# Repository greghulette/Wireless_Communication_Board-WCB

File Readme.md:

<h1 style="display:inline; height: 75px; font-size:51px;">Wireless Communication Board (WCB)</h1>

<br>

# Software 3.0 and newer release changes the command structure.  Please read below to ensure proper operations.  

**NEW WIKI created to help better orgainize the documenation.  It can be found at the top the page or by clicking this link: [WCB Wiki](https://github.com/greghulette/Wireless_Communication_Board-WCB/wiki/)**

<br>
<br>
<br>
<br>
<br>

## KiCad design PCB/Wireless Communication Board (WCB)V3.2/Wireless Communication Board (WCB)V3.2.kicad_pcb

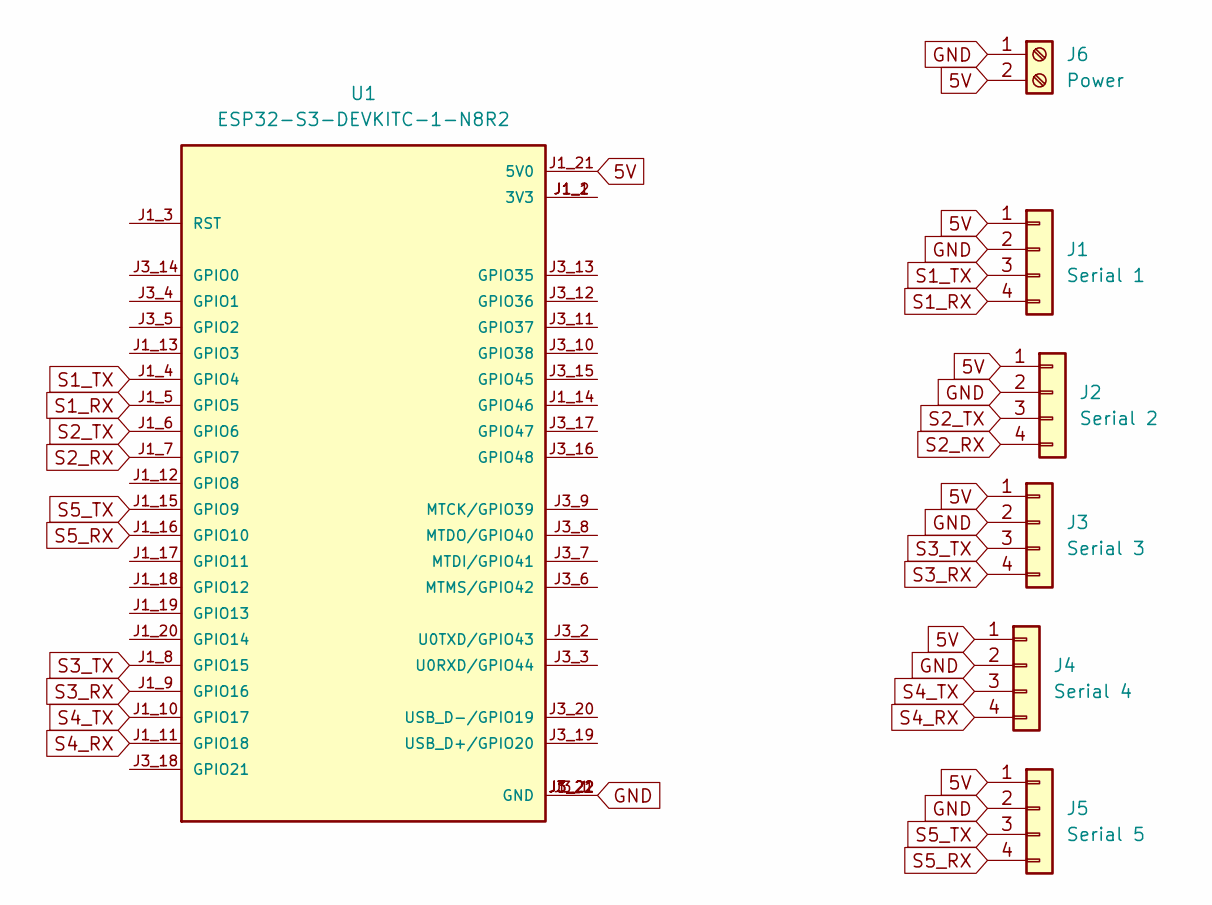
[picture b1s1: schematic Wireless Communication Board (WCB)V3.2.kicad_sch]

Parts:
J1: Serial 1; PinHeader_1x04_P2.54mm_Vertical
J2: Serial 2; PinHeader_1x04_P2.54mm_Vertical
J3: Serial 3; PinHeader_1x04_P2.54mm_Vertical
J4: Serial 4; PinHeader_1x04_P2.54mm_Vertical
J5: Serial 5; PinHeader_1x04_P2.54mm_Vertical
J6: Power; TerminalBlock_Phoenix_MKDS-1,5-2-5.08_1x02_P5.08mm_Horizont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
U1: ESP32-S3-DEVKITC-1-N8R2; XCVR_ESP32-S3-DEVKITC-1-N8R2; PARTREV V1

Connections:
5V: J1.1, J2.1, J3.1, J4.1, J5.1, J6.2, U1.J1_21 (5V0)
GND: J1.2, J2.2, J3.2, J4.2, J5.2, J6.1, U1.J1_22 (GND), U1.J3_1 (GND), U1.J3_21 (GND), U1.J3_22 (GND)
unnamed: U1.J1_1 (3V3), U1.J1_2 (3V3)
S1_RX: J1.4, U1.J1_5 (GPIO5)
S1_TX: J1.3, U1.J1_4 (GPIO4)
S2_RX: J2.4, U1.J1_7 (GPIO7)
S2_TX: J2.3, U1.J1_6 (GPIO6)
S3_RX: J3.4, U1.J1_9 (GPIO16)
S3_TX: J3.3, U1.J1_8 (GPIO15)
S4_RX: J4.4, U1.J1_11 (GPIO18)
S4_TX: J4.3, U1.J1_10 (GPIO17)
S5_RX: J5.4, U1.J1_16 (GPIO10)
S5_TX: J5.3, U1.J1_15 (GPIO9)

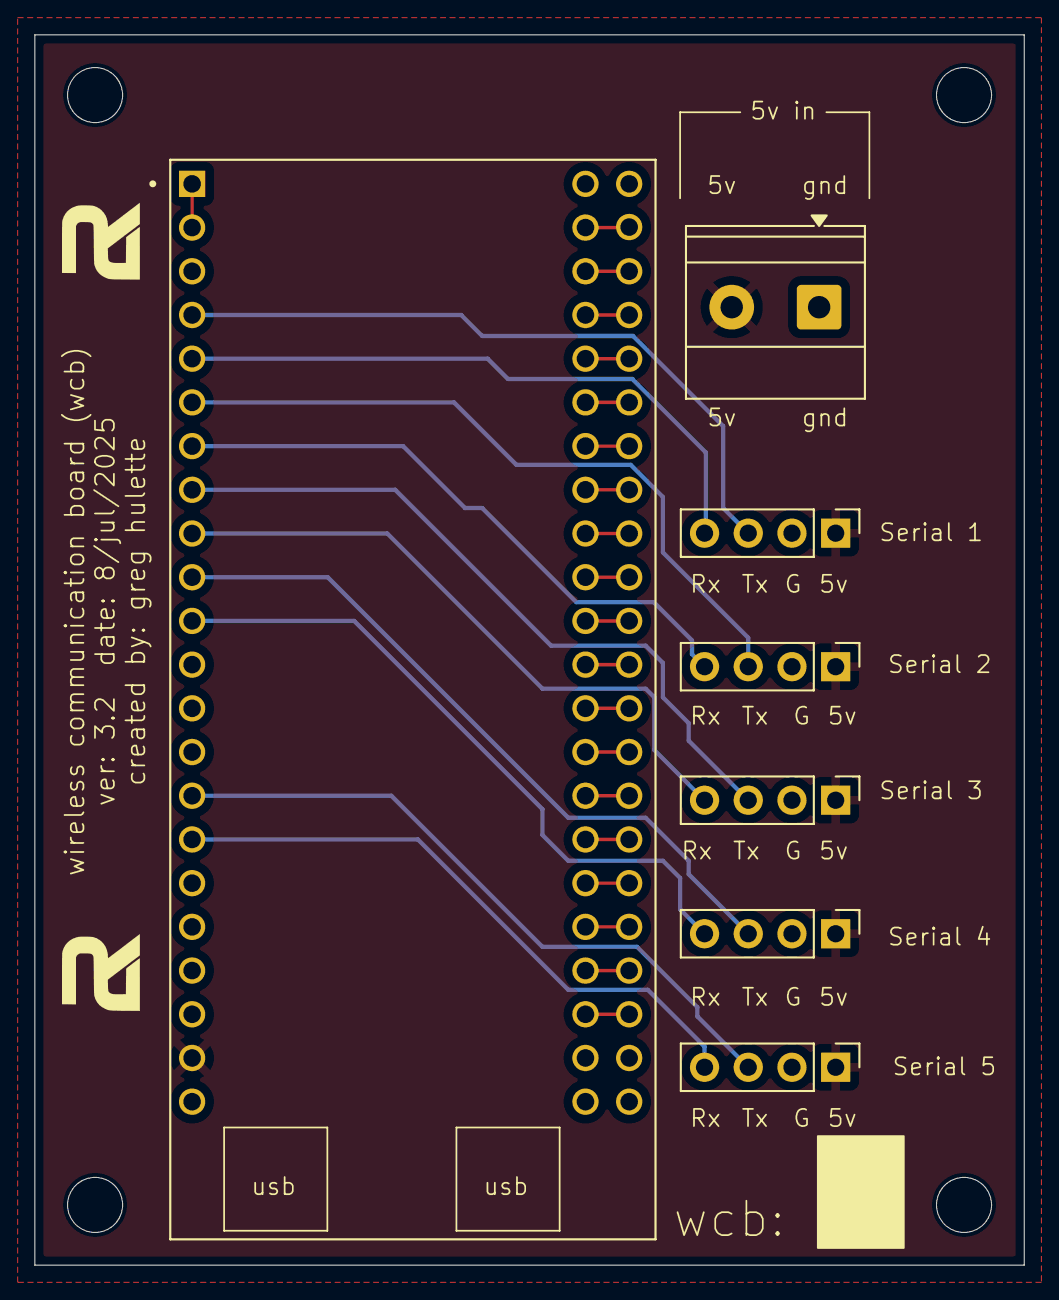
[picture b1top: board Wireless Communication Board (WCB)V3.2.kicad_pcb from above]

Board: 2 copper layers, 57.5 x 71.5 mm, 7 parts (0 on the bottom side), 13 nets.

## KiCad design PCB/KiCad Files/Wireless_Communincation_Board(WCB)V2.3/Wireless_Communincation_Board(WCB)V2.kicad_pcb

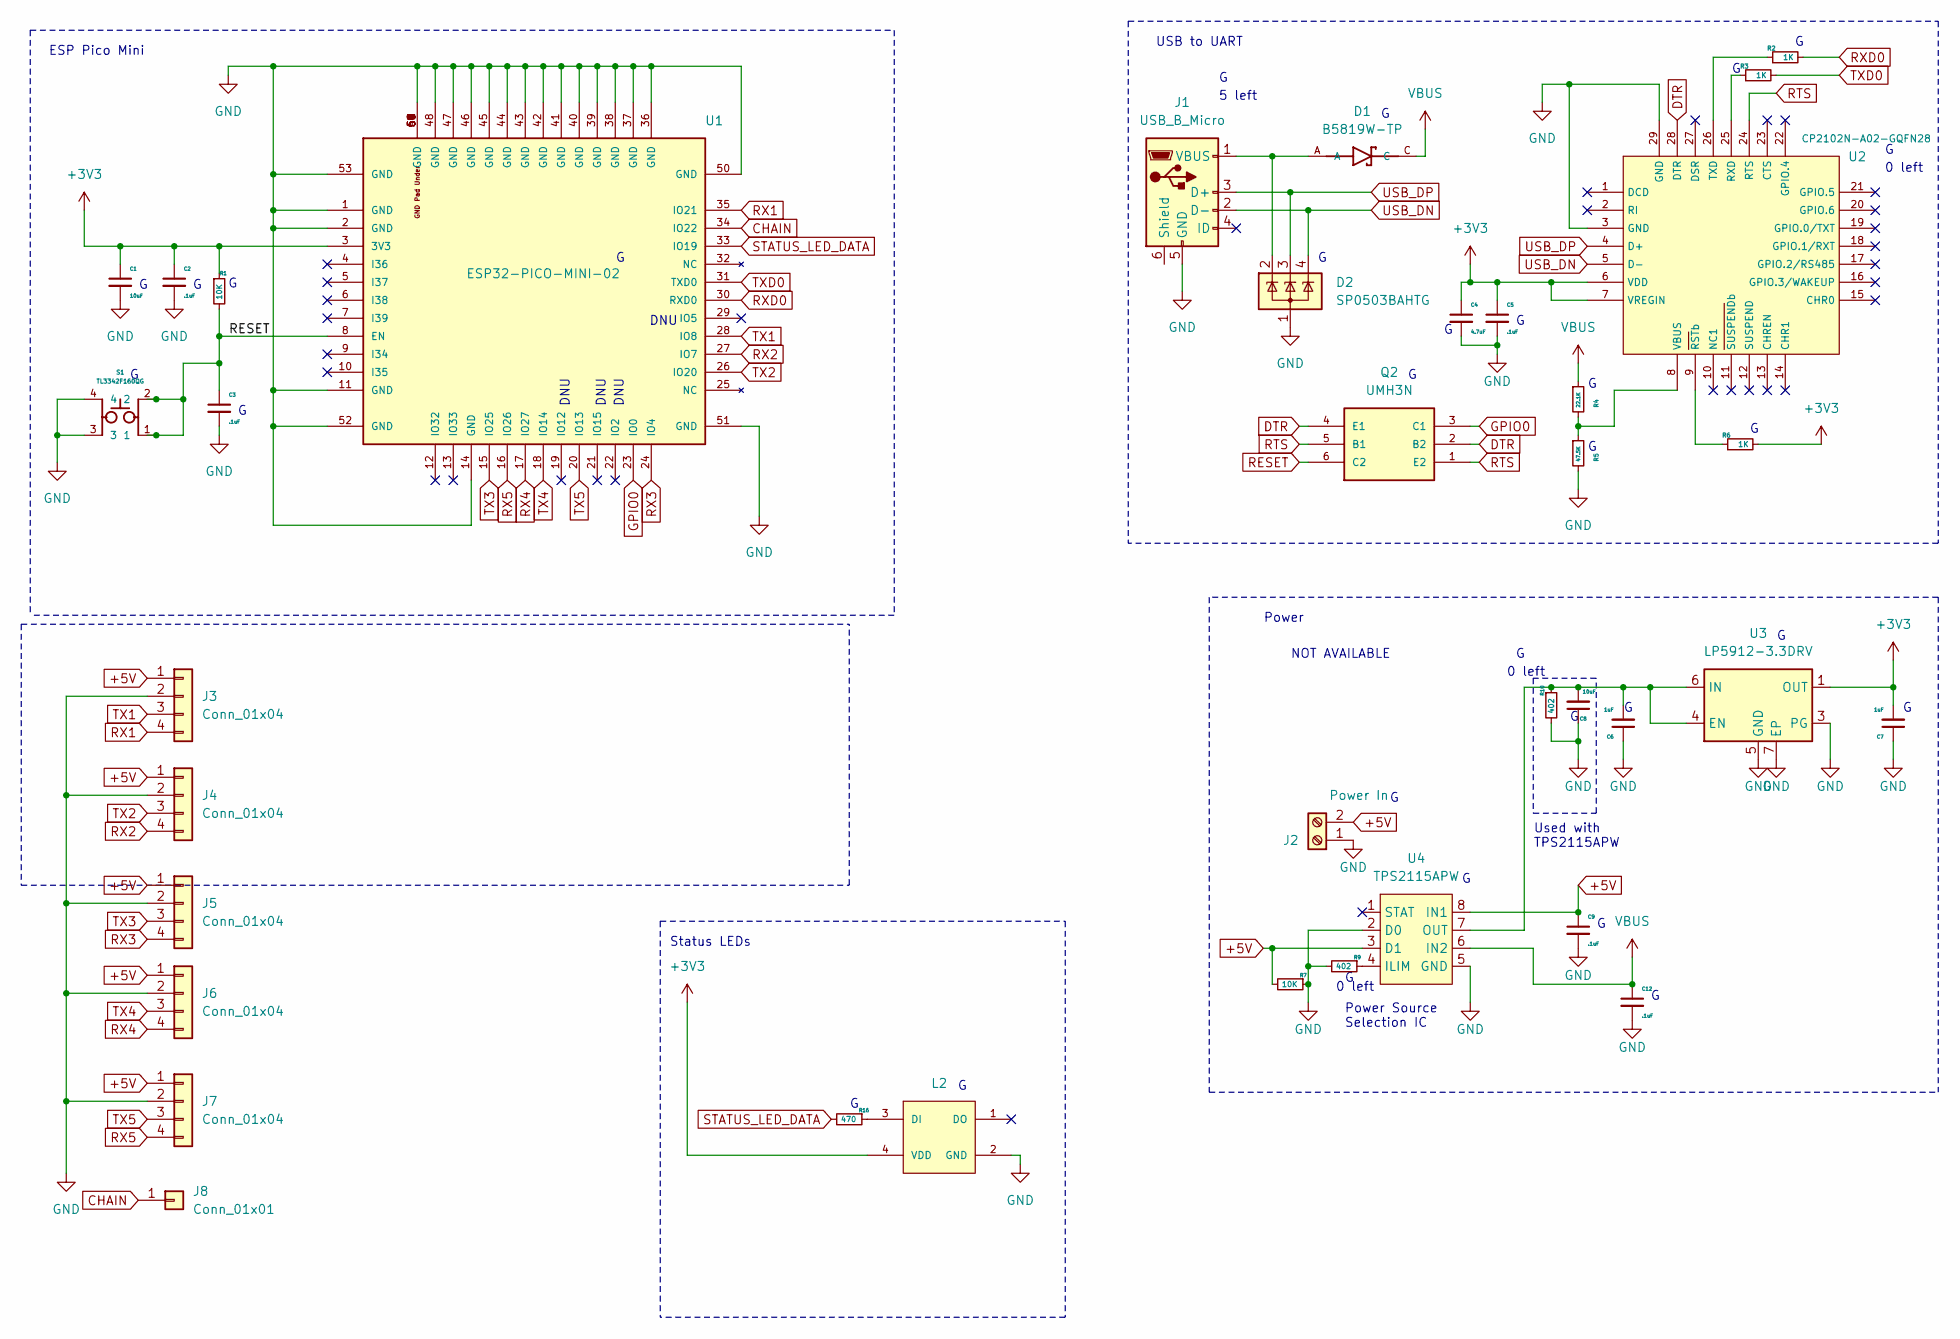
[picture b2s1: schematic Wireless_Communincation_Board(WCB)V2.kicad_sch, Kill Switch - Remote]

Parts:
C1, C8: 10uF; C_0805_2012Metric; Manufacturers Part Numb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 CS2012X7R106K100NRE; LCSC C1222438
C2, C3, C5, C9, C12: .1uF; C_0402_1005Metric; Manufacturers Part Numb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 CL05B104KB54PNC; LCSC C307331
C4: 4.7uF; C_0805_2012Metric; Manufacturers Part Numb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 GCM21BR71C475KA67L; LCSC C126590
C6, C7: 1uF; C_0603_1608Metric; Manufacturers Part Numb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 GRM188B31H105KAALD; LCSC C913562
D1: B5819W-TP; SOD3716X135N; Manufacturers Part Numb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 B5819W-TP; Digikey Part Number B5819W-TPMSCT-ND
D2: SP0503BAHTG; SOT-143; Manufacturers Part Numb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 SP0503BAHTG; Digikey Part Number F2715CT-ND
J1: USB_B_Micro; USB_Micro-B_Amphenol_10118194_Horizontal; Manufacturers Part Numb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 10118194-0001LF; Digikey Part Number 609-4618-1-ND
J2: Power In; TerminalBlock_bornier-2_P5.08mm; Manufacturers Part Numb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 141-A-111/02; LCSC C3011914
J3, J4, J5, J6, J7: Conn_01x04; PinHeader_1x04_P2.54mm_Vertical; LCSC C2691448
J8: Conn_01x01; PinHeader_1x01_P2.54mm_Vertical; LCSC C81276
L2: WS2812B-2020; Manufacturers Part Numb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 WS2812B-2020; LCSC C965555
Q2: UMH3N; SOT65P230X110-6N; MANUFACTURER_PART_NUMBER UMH3N; Digikey Part Number UMH3NTNCT-ND
R1: 10K; R_0402_1005Metric; Manufacturers Part Numb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 RC0402JR-0710KL; Digikey Part Number 311-10KJRCT-ND
R2, R3, R6: 1K; R_0402_1005Metric; Manufacturers Part Numb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 RC0402JR-071KL; Digikey Part Number 311-1.0KJRCT-ND
R4: 22.1K; R_0402_1005Metric; Manufacturers Part Numb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 RC0402JR-0722KL; Digikey Part Number 311-22KJRCT-ND
R5: 47.5K; R_0402_1005Metric; Manufacturers Part Numb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 RC0402FR-0747K5L; Digikey Part Number 311-47.5KLRCT-ND
R7: 10K; R_0402_1005Metric; Manufacturers Part Numb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 AR02DTC1002; LCSC C414854
R9, R10: 402; R_0402_1005Metric; Manufacturers Part Numb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 CR204000F; LCSC C41042
R16: 470; R_0402_1005Metric; Manufacturers Part Numb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 RT0402BRD07470RL; LCSC C114949
S1: TL3342F160QG; SW_TL3342F160QG; Manufacturers Part Numb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 TS-1076S-A6B3; LCSC C492949
U1: ESP32-PICO-MINI-02; MODULE_ESP32-PICO-MINI-02; PARTREV v1.0; Digikey Part Number 1965-ESP32-PICO-MINI-02-N8R2CT-ND
U2: CP2102N-A02-GQFN28; QFN-28-1EP_5x5mm_P0.5mm_EP3.35x3.35mm; Manufacturers Part Numb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 CP2102N-A02-GQFN28; Digikey Part Number 336-5889-ND
U3: LP5912-3.3DRV; WSON-6-1EP_2x2mm_P0.65mm_EP1x1.6mm_ThermalVias; Manufacturers Part Numb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 LP5912Q3.3DRVTQ1; LCSC C2876187
U4: TPS2115APW; TSSOP-8_4.4x3mm_P0.65mm; Manufacturers Part Numb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 TPS2115APWR; Digikey Part Number 296-26918-5-ND

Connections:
+3V3: C1.1, C2.1, C4.1, C5.1, C7.2, L2.4 (VDD), R1.1, R6.2, U1.3 (3V3), U2.6 (VDD), U2.7 (VREGIN), U3.1 (OUT)
+5V: C9.1, J2.2, J3.1, J4.1, J5.1, J6.1, J7.1, R7.2, U4.3 (D1), U4.8 (IN1)
CHAIN: J8.1, U1.34 (IO22)
DTR: Q2.2 (B2), Q2.4 (E1), U2.28 (DTR)
GND: C1.2, C2.2, C3.2, C4.2, C5.2, C6.1, C7.1, C8.1, C9.2, C12.2, D2.1 (A), J1.5 (GND), J2.1, J3.2, J4.2, J5.2, J6.2, J7.2, L2.2 (GND), R5.2, R7.1, R9.2, R10.2, S1.3, S1.4, U1.1 (GND), U1.2 (GND), U1.11 (GND), U1.14 (GND), U1.36 (GND), U1.37 (GND), U1.38 (GND), U1.39 (GND), U1.40 (GND), U1.41 (GND), U1.42 (GND), U1.43 (GND), U1.44 (GND), U1.45 (GND), U1.46 (GND), U1.47 (GND), U1.48 (GND), U1.49 (GND), U1.50 (GND), U1.51 (GND), U1.52 (GND), U1.53 (GND), U1.54 (GND), U1.55 (GND), U1.56 (GND), U1.57 (GND), U1.58 (GND), U1.59 (GND), U1.60 (GND), U1.61 (GND), U2.3 (GND), U2.29 (GND), U3.3 (PG), U3.5 (GND), U3.7 (EP), U4.2 (D0), U4.5 (GND)
GPIO0: Q2.3 (C1), U1.23 (IO0)
unnamed: C6.2, C8.2, R10.1, U3.4 (EN), U3.6 (IN), U4.7 (OUT)
unnamed: D1.A, D2.2 (K), J1.1 (VBUS)
unnamed: L2.3 (DI), R16.1
unnamed: R2.1, U2.26 (TXD)
unnamed: R3.1, U2.25 (RXD)
unnamed: R4.2, R5.1, U2.8 (VBUS)
unnamed: R6.1, U2.9 (RSTb)
unnamed: R9.1, U4.4 (ILIM)
RESET: C3.1, Q2.6 (C2), R1.2, S1.1, S1.2, U1.8 (EN)
RTS: Q2.1 (E2), Q2.5 (B1), U2.24 (RTS)
RX1: J3.4, U1.35 (IO21)
RX2: J4.4, U1.27 (IO7)
RX3: J5.4, U1.24 (IO4)
RX4: J6.4, U1.17 (IO27)
RX5: J7.4, U1.16 (IO26)
RXD0: R2.2, U1.30 (RXD0)
STATUS_LED_DATA: R16.2, U1.33 (IO19)
TX1: J3.3, U1.28 (IO8)
TX2: J4.3, U1.26 (IO20)
TX3: J5.3, U1.15 (IO25)
TX4: J6.3, U1.18 (IO14)
TX5: J7.3, U1.20 (IO13)
TXD0: R3.2, U1.31 (TXD0)
USB_DN: D2.4 (K), J1.2 (D-), U2.5 (D-)
USB_DP: D2.3 (K), J1.3 (D+), U2.4 (D+)
VBUS: C12.1, D1.C, R4.1, U4.6 (IN2)

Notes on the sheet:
0 left
Power
DNU
ESP Pico Mini
NOT AVAILABLE
5 left
Power Source Selection IC
Status LEDs
Used with TPS2115APW
USB to UART

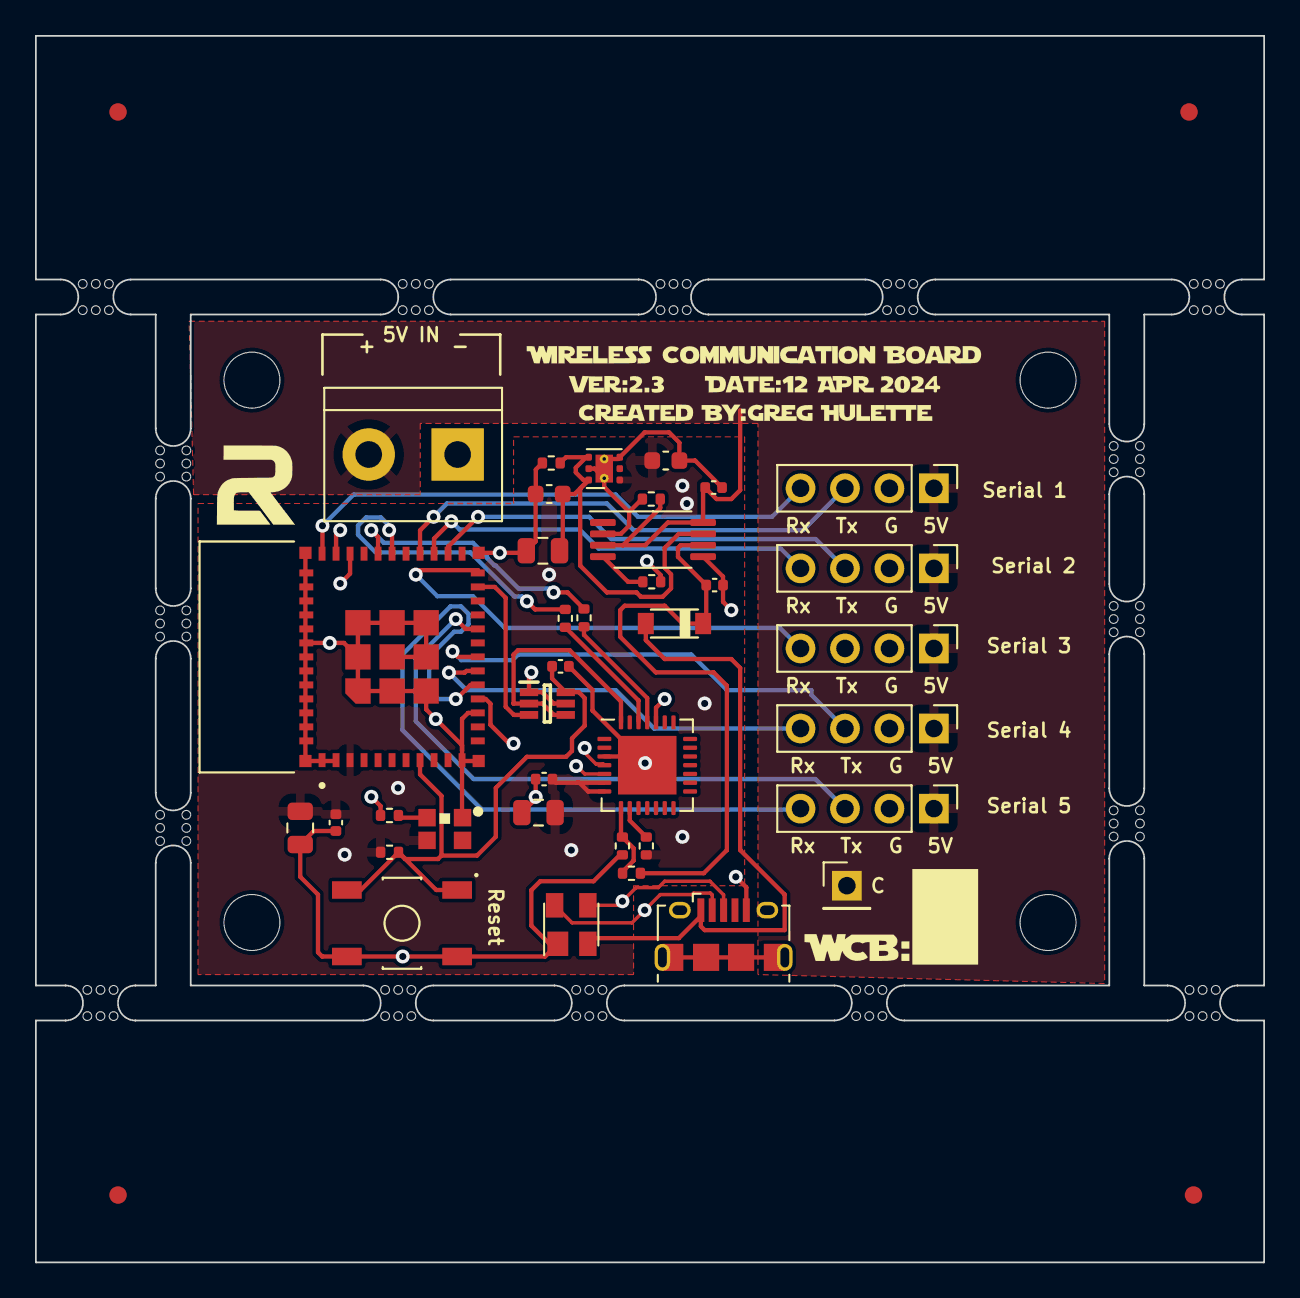
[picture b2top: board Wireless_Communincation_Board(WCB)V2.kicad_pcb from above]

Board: 4 copper layers, 70.2 x 70.1 mm, 53 parts (0 on the bottom side), 32 nets.

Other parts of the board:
mouse-bite-2mm-slot, mouse-bite-2mm-slot#2, mouse-bite-2mm-slot#3, mouse-bite-2mm-slot#4, mouse-bite-2mm-slot#5, mouse-bite-2mm-slot#6, mouse-bite-2mm-slot#7, mouse-bite-2mm-slot#8, mouse-bite-2mm-slot#9, mouse-bite-2mm-slot#10, mouse-bite-2mm-slot#11, mouse-bite-2mm-slot#12, mouse-bite-2mm-slot#13, mouse-bite-2mm-slot#14, mouse-bite-2mm-slot#15, mouse-bite-2mm-slot#16: VAL**; mouse-bite-2mm-slot

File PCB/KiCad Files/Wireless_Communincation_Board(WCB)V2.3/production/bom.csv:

Designator,Footprint,Quantity,Value,LCSC Part #
C1,0805,1,10uF,C1222438
C12,0402,1,.1uF,C307331
C2,0402,1,.1uF,C307331
C3,0402,1,.1uF,C307331
C4,0805,1,4.7uF,C126590
C5,0402,1,.1uF,C307331
C6,0603,1,1uF,C913562
C7,0603,1,1uF,C913562
C8,0805,1,10uF,C1222438
C9,0402,1,.1uF,C307331 
D1,SOD3716X135N,1,B5819W-TP,C84354
D2,SOT-143,1,SP0503BAHTG,C7074
J1,USB_Micro-B_Amphenol_10118194_Horizontal,1,USB_B_Micro,C132563
J2,TerminalBlock_bornier-2_P5.08mm,1,Power In,C3011914
"J3, J4, J5, J6, J7",PinHeader_1x04_P2.54mm_Vertical,5,Conn_01x04,C2691448
J8,PinHeader_1x01_P2.54mm_Vertical,1,Conn_01x01,
L2,WS2812B-2020,1,WS2812B-2020,C965555
Q2,SOT65P230X110-6N,1,UMH3N,C123008
R1,0402,1,10K,C60489
R10,0402,1,402,C41042
R16,0402,1,470,C114949
R2,0402,1,1K,C105637
R3,0402,1,1K,C105637
R4,0402,1,22.1K,C137898
R5,0402,1,47.5K,C319605
R6,0402,1,1K,C105637
R7,0402,1,10K,C414854
R9,0402,1,402,C41042
S1,SW_TL3342F160QG,1,TL3342F160QG,C492949
U1,MODULE_ESP32-PICO-MINI-02,1,ESP32-PICO-MINI-02,C2980306
U2,QFN-28-1EP_5x5mm_P0.5mm_EP3.35x3.35mm,1,CP2102N-A02-GQFN28,C964632
U3,WSON-6-1EP_2x2mm_P0.65mm_EP1x1.6mm_ThermalVias,1,LP5912-3.3DRV,C2876187
U4,TSSOP-8_4.4x3mm_P0.65mm,1,TPS2115APW,C70287
"mouse-bite-2mm-slot_16, mouse-bite-2mm-slot_15, mouse-bite-2mm-slot_14, mouse-bite-2mm-slot_13, mouse-bite-2mm-slot_12, mouse-bite-2mm-slot_11, mouse-bite-2mm-slot_10, mouse-bite-2mm-slot_9, mouse-bite-2mm-slot_8, mouse-bite-2mm-slot_7, mouse-bite-2mm-slot_6, mouse-bite-2mm-slot_5, mouse-bite-2mm-slot_4, mouse-bite-2mm-slot_3, mouse-bite-2mm-slot_2, mouse-bite-2mm-slot",mouse-bite-2mm-slot,16,VAL**,

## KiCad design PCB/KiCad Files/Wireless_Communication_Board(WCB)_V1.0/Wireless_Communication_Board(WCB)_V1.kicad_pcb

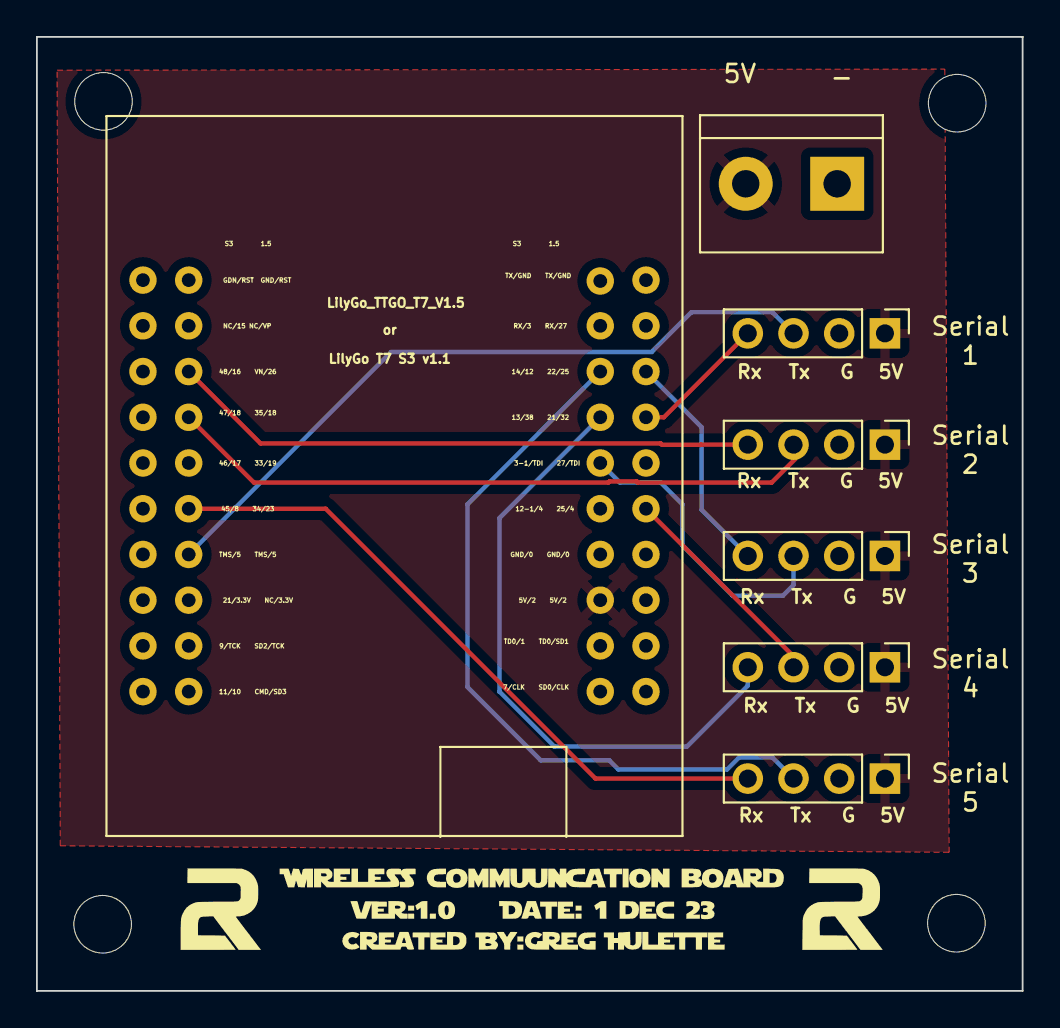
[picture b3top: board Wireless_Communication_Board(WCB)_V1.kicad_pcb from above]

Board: 2 copper layers, 54.8 x 53.0 mm, 7 parts (0 on the bottom side), 12 nets.

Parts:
J1: S1; PinHeader_1x04_P2.54mm_Vertical
J2: S2; PinHeader_1x04_P2.54mm_Vertical
J3: S3; PinHeader_1x04_P2.54mm_Vertical
J4: S4; PinHeader_1x04_P2.54mm_Vertical
J5: S5; PinHeader_1x04_P2.54mm_Vertical
J6: Screw_Terminal_01x02; TerminalBlock_bornier-2_P5.08mm
U1: LilyGo_TTGO_T7_V1.5; LILYGO_TTGO_T7_V1.5

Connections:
+5V: J1.1, J2.1, J3.1, J4.1, J5.1, J6.2, U1.70 (5V)
GND: J1.2, J2.2, J3.2, J4.2, J5.2, J6.1, U1.60 (GND), U1.61 (GND), U1.62 (GND)
Rx1: J1.4, U1.32 (GPIO32)
Rx2: J2.4, U1.26 (GPIO26)
Rx3: J3.4, U1.251 (GPIO25_1)
Rx4: J4.4, U1.21 (GPIO21)
Rx5: J5.4, U1.23 (GPIO23)
Tx1: J1.3, U1.5 (GPIO5)
Tx2: J2.3, U1.18 (GPIO18)
Tx3: J3.3, U1.27 (GPIO27)
Tx4: J4.3, U1.4 (GPIO4)
Tx5: J5.3, U1.22 (GPIO22)
